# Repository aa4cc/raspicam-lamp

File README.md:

# Raspberry Pi Camera Lamp

## Overall concept

The main part of the light are two branches with 12 LEDs each. They are arranged in 2 concentric circles. In the centre of these circles there is a hole (7mm diameter) for camera lens. In the space between this hole and the LEDs there are 4 mounting holes for attaching the camera to the board. Beneath this "circular" part there is a "rectangular" part of the light controller. Taking from left to right, there are two inductors, two Schottky diodes, two LED drivers, two resistors and two capacitors and the data (PWM) connector, the power connector and a trimmer and a solder jumper. There are altogether 6 holes for mounting the whole module (light board + camera) to a holder. The wiring is based on a schematic shown in the datasheet of the AP8801 driver.

Here you can see the [3D model of the board](https://a360.co/2OzGw6O).

Here is the [schematic and board](https://cadlab.io/project/1334).

## Components
 (numbers hold for one board)

 |	Part				|	Manufacturer	|	Manufacturer No.			|	Farnell/Mouser Ref.			|	Pieces	|
 |	-----				|	-----			|	-----						|	-----						|	-----	|
 |	LED 				|	OSRAM			|	GW JDSTS2.EM-H4H7-XX33-1 	|	<https://bit.ly/2IQPlnt>	|	24		|
 |	LED driver 			|	DIODES 			|	AP8801 						|	<https://bit.ly/2E9jP5u>	|	2		|
 |	Capacitor 			|	TAIYO YUDEN 	|	HMK325BJ475KN-TE 			|	<https://bit.ly/2Oex5dw> 	|	2		|
 |	Inductor 			|	BOURNS 			|	SRN8040TA-101M 				|	<https://bit.ly/2NzDQ4y> 	|	2		|
 |	Resistor 1R1		|	KOA SPEER 		|	RK73H1JTTD1R10F 			|	<https://bit.ly/2QF4E5e>	|	2		|
 |	Schottky Rectifier 	|	VISHAY 			|	SS1H10-E3/61T 				|	<https://bit.ly/2ywoOXw>	|	2		|
 |	Trimmer 			|	BOURNS 			|	TC33X-2-103E 				|	<https://bit.ly/2yaW6MC>	|	1		|

The values of the components were determined based on the LED driver (AP8801) datasheet.

### Connectors

- POWER-1 - +48V
- POWER-2 - GND
- CTRL-1 - GND
- CTRL-2 - RASPBERRY Pi PWM 
- CTRL-3 - RASPBERRY Pi PWM 

## Assembly

As our light board is made of aluminium and the heat dissipates massively, we recommend to solder the LEDs as shown in the following picture:

The board is heated with hot air from beneath and the solder pad gets heated from the soldering iron.

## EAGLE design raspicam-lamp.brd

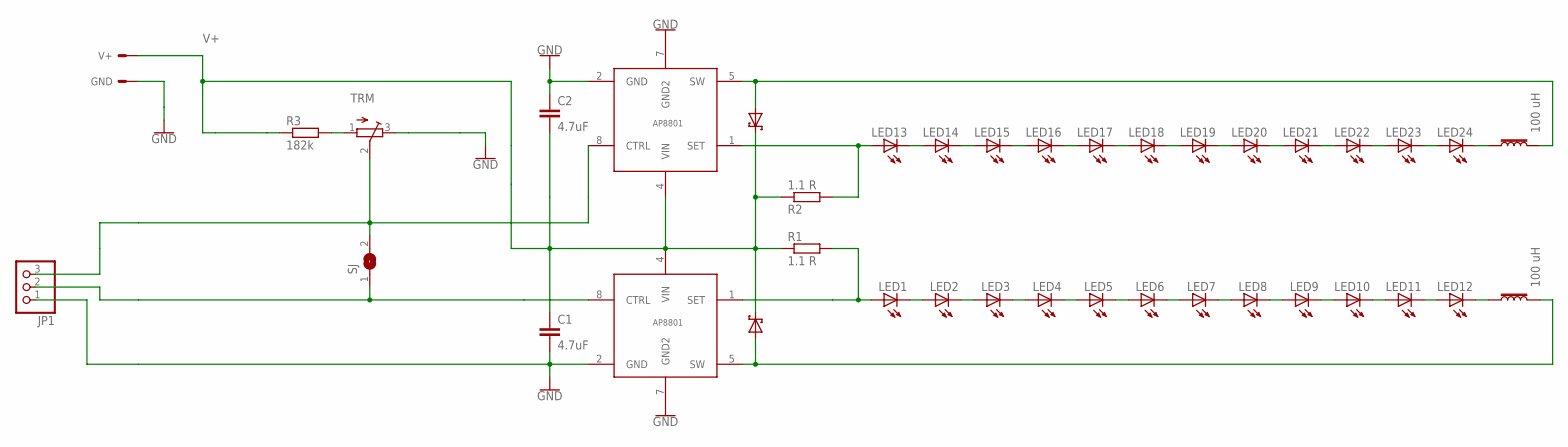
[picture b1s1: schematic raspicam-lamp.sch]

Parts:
C1, C2: 4.7uF; C3225
GND: PWR_PAD; PWR_PAD_FP
JP1: PINHD-1X03_2.54-SMD-90°; 1X03SMD/90
L1, L2: 100 uH; SRN8040TA-101M
LED1, LED2, LED3, LED4, LED5, LED6, LED7, LED8, LED9, LED10, LED11, LED12, LED13, LED14, LED15, LED16, LED17, LED18, LED19, LED20, LED21, LED22, LED23, LED24: GW-JDSTS2.EM
R1, R2: 1.1 R; R0603
R3: 182k; R0603
SD1, SD2: SCHOTTKY-DO-2014AC; SCHOTTKY-DO-214AC
SJ: SJ
TRM: TRIMPOTTC33X; TC33X
U$1, U$2: AP8801; SO08
V+: PWR_PAD; PWR_PAD_FP

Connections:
GND: C1.2, C2.1, GND.P$1, JP1.1, TRM.3 (E), U$1.2 (GND), U$1.7 (GND2), U$2.2 (GND), U$2.7 (GND2)
unnamed: L1.2, SD2.A, U$2.5 (SW)
unnamed: LED1.A, R1.2, U$1.1 (SET)
unnamed: JP1.2, SJ.1, U$1.8 (CTRL)
unnamed: R3.2, TRM.1 (A)
unnamed: JP1.3, SJ.2, TRM.2 (S), U$2.8 (CTRL)
unnamed: L2.2, SD1.A, U$1.5 (SW)
unnamed: LED13.A, R2.2, U$2.1 (SET)
unnamed: LED1.C, LED2.A
unnamed: LED2.C, LED3.A
unnamed: LED3.C, LED4.A
unnamed: LED4.C, LED5.A
unnamed: LED5.C, LED6.A
unnamed: LED6.C, LED7.A
unnamed: LED7.C, LED8.A
unnamed: LED8.C, LED9.A
unnamed: LED9.C, LED10.A
unnamed: LED10.C, LED11.A
unnamed: LED11.C, LED12.A
unnamed: LED13.C, LED14.A
unnamed: LED14.C, LED15.A
unnamed: LED15.C, LED16.A
unnamed: LED16.C, LED17.A
unnamed: LED17.C, LED18.A
unnamed: LED18.C, LED19.A
unnamed: LED19.C, LED20.A
unnamed: LED20.C, LED21.A
unnamed: LED21.C, LED22.A
unnamed: LED22.C, LED23.A
unnamed: LED23.C, LED24.A
unnamed: L2.1, LED12.C
unnamed: L1.1, LED24.C
V+: C1.1, C2.2, R1.1, R2.1, R3.1, SD1.C, SD2.C, U$1.4 (VIN), U$2.4 (VIN), V+.P$1

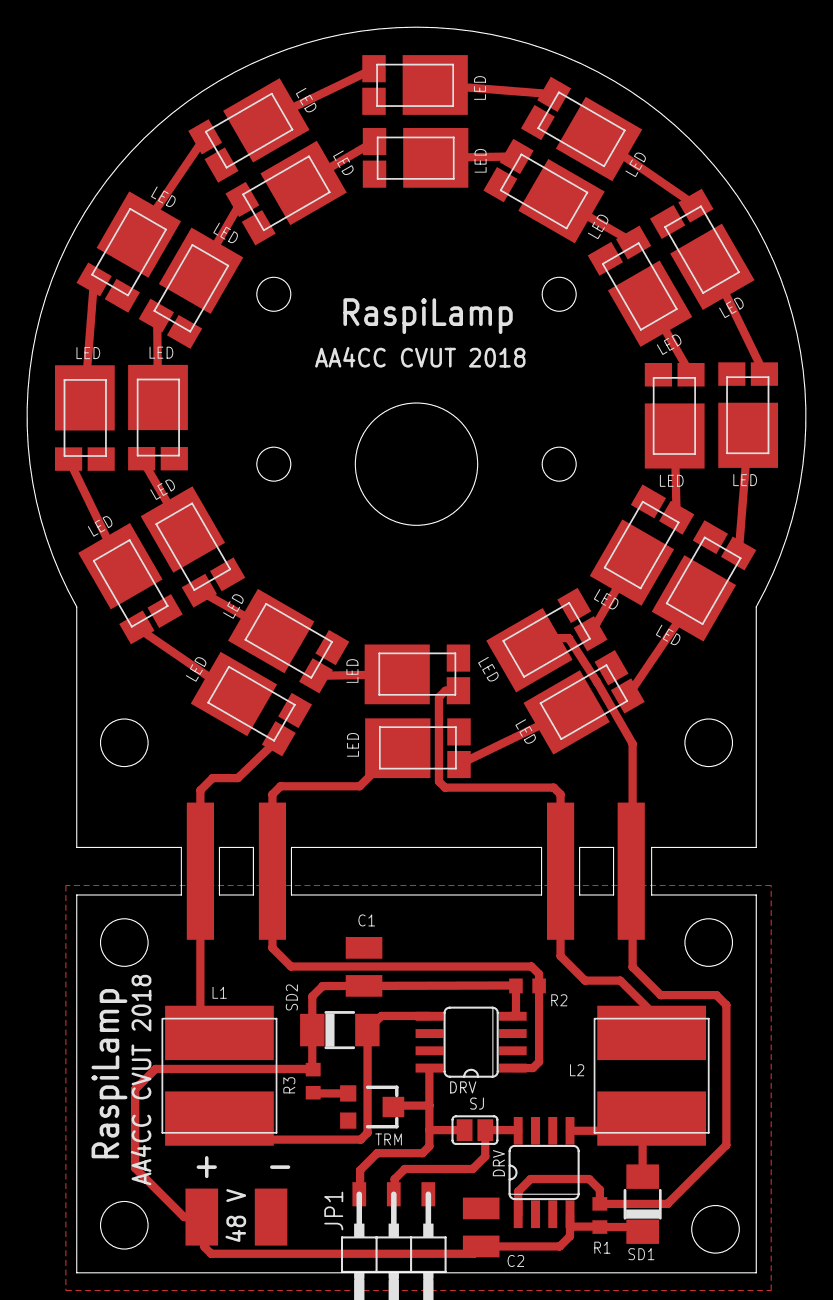
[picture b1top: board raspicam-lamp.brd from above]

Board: 2 copper layers, 57.3 x 91.7 mm, 40 parts (0 on the bottom side), 33 nets.

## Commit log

2018-10-01 Initial version
2018-10-01 Backlink to CADLAB.io has been added.
2018-10-10 README edit and img
2018-10-12 New LED ref

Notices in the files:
parts and their libraries:
SparkFun-PowerSymbols: Licensing: Creative Commons ShareAlike 4.0 International - https://creativecommons.org/licenses/by-sa/4.0
